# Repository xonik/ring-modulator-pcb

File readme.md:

# Yusynth Ring modulator

http://yusynth.net/Modular/EN/RINGMOD/index.html

All text is from Yusynth

## Description

The balanced modulator or four quadrant multiplier, is a great classical module. it provides the same functions as those of a ring modulator. Its main purpose is to generate  sounds with a complex overtone content such as bell sounds and other klang tones !
The principle of this circuit is based on a Gilbert cell (see references at the end of this page) contained in the classical LM1496 IC.

Basically, if one feeds the A input with a sinewave with frequency f1, that is sin(2πf1), and the B input with a sinewave with frequenc f2, that is sin(2πf2), one gets at the output the product these two signals, that is sin(2πf1) x sin(2πf2).

Due to trigonomic properties it reads :

 sin(2πf1) x sin(2πf2) = sin(2π(f1+f2)) + sin(2π(f1-f2))

in other words the output is a mixture of two sinewaves, one with frequency f1+f2 and the other with frequency f1-f2.

## Schematic

The schematic of this balanced modulator is directly inspired by that of the Elektor's Formant  (which is a mere adaptation of the application schematic of the LM1496 datasheet, see at the end of this page). I have only changed the values of the input resistors in order to make the input signal levels compatible with the Moog/Dotcom standards (10V peak to peak) I also added an output stage that amplifies the output signal by 6.8 in order to obtain 10Vpp.

## Settings and trimming

There are four trimmers to adjust : A1 to A4. These trimmers are used for cancelling the input signals. The settings are quite simple, you will need a signal generator that delivers a sinewave signal with a 10V (peak to peak) output amplitude. Here is how to proceed :
Tune the generator on 1000Hz and set the output level of the generator to 10Vpp.

Connect the output AxB (or CxD) of the module to an audio amplifier. Be sure to set the input potentiometer of the amplifier to a low value : the output level of the module is 10Vpp and most of the audio amplifiers expect an input level that doesn't exceed 1Vpp.
Connect the signal generator to the input A (or C) with a capacitor (AC-INPUT). There, you must hxear the 1000Hz signal at the output AxB (or CxD).

Adjust the trimmer A2 (or A4) such that the 1000Hz signal can no longer be heard at the output.

Disconnect the signal generator from input A (or C) and then connect the signal generator to the input B (or D)  with a capacitor (AC-INPUT). There, you must hear the 1000Hz signal at the output AxB (or CxD).
Adjust the trimmer A1 (or A3) such that the 1000Hz signal can no longer be heard at the output.

Now the module is ready to operate. A last check can be done by connecting the 1000Hz signal to both inputs A and B (AC inputs) : there you must hear a single signal of frequency twice as high (2000Hz).

**Comment (JT): A1 and A3 are the 470/500 ohm pots, A2 and A4 are 200/220 ohm.**

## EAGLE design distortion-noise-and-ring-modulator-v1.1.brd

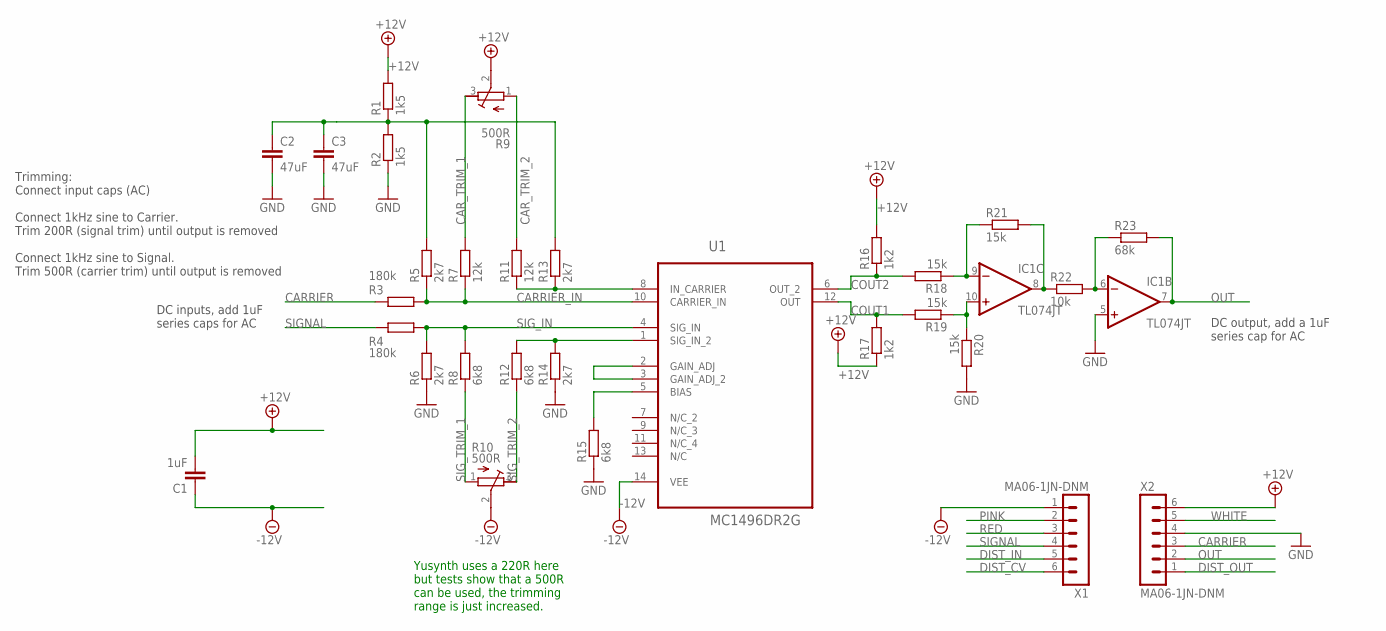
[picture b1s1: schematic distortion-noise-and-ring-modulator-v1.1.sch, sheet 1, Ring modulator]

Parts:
C1: 1uF; C0402-J
C2, C3: 47uF; C1206
IC1: TL074JT; TSSOP14J
R1, R2: 1k5; R0402
R3, R4: 180k; R0402
R5, R6, R13, R14: 2k7; R0603
R7, R11: 12k; R0402
R8, R12, R15: 6k8; R0603
R9, R10: 500R; RTRIM3296X
R16, R17: 1k2; R0603
R18, R19, R20, R21: 15k; R0402
R22: 10k; R0402
R23: 68k; R0603
U1: MC1496DR2G; SOIC127P600X175-14N
X1, X2: MA06-1JN-DNM; MA06N-1J

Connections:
+12V: C1.2, R1.2, R9.2 (S), R16.2, R17.1, X2.6; also elsewhere on the board
-12V: C1.1, R10.2 (S), U1.14 (VEE), X1.1; also elsewhere on the board
CARRIER: R3.1, X2.3
CARRIER_IN: R3.2, R5.1, R7.1, U1.10 (CARRIER_IN)
CAR_TRIM_1: R7.2, R9.3 (E)
CAR_TRIM_2: R9.1 (A), R11.2
COUT1: R17.2, R19.2, U1.12 (OUT)
COUT2: R16.1, R18.2, U1.6 (OUT_2)
DIST_CV: X1.6; also elsewhere on the board
DIST_IN: X1.5; also elsewhere on the board
DIST_OUT: X2.1; also elsewhere on the board
GND: C2.2, C3.2, IC1.5 (+IN), R2.1, R6.1, R14.1, R15.1, R20.2, X2.4; also elsewhere on the board
unnamed: R12.2, R14.2, U1.1 (SIG_IN_2)
unnamed: R11.1, R13.1, U1.8 (IN_CARRIER)
unnamed: C2.1, C3.1, R1.1, R2.2, R5.2, R13.2
unnamed: R15.2, U1.5 (BIAS)
unnamed: U1.2 (GAIN_ADJ), U1.3 (GAIN_ADJ_2)
unnamed: IC1.10 (+IN), R19.1, R20.1
unnamed: IC1.9 (-IN), R18.1, R21.1
unnamed: IC1.8 (OUT), R21.2, R22.1
unnamed: IC1.6 (-IN), R22.2, R23.1
OUT: IC1.7 (OUT), R23.2, X2.2
PINK: X1.2; also elsewhere on the board
RED: X1.3; also elsewhere on the board
SIGNAL: R4.1, X1.4
SIG_IN: R4.2, R6.2, R8.2, U1.4 (SIG_IN)
SIG_TRIM_1: R8.1, R10.1 (A)
SIG_TRIM_2: R10.3 (E), R12.1
WHITE: X2.5; also elsewhere on the board

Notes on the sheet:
DC inputs, add 1uF series caps for AC
DC output, add a 1uF series cap for AC
Trimming: Connect input caps (AC) Connect 1kHz sine to Carrier. Trim 200R (signal trim) until output is removed Connect 1kHz sine to Signal. Trim 500R (carrier trim) until output is removed
Yusynth uses a 220R here but tests show that a 500R can be used, the trimming range is just increased.

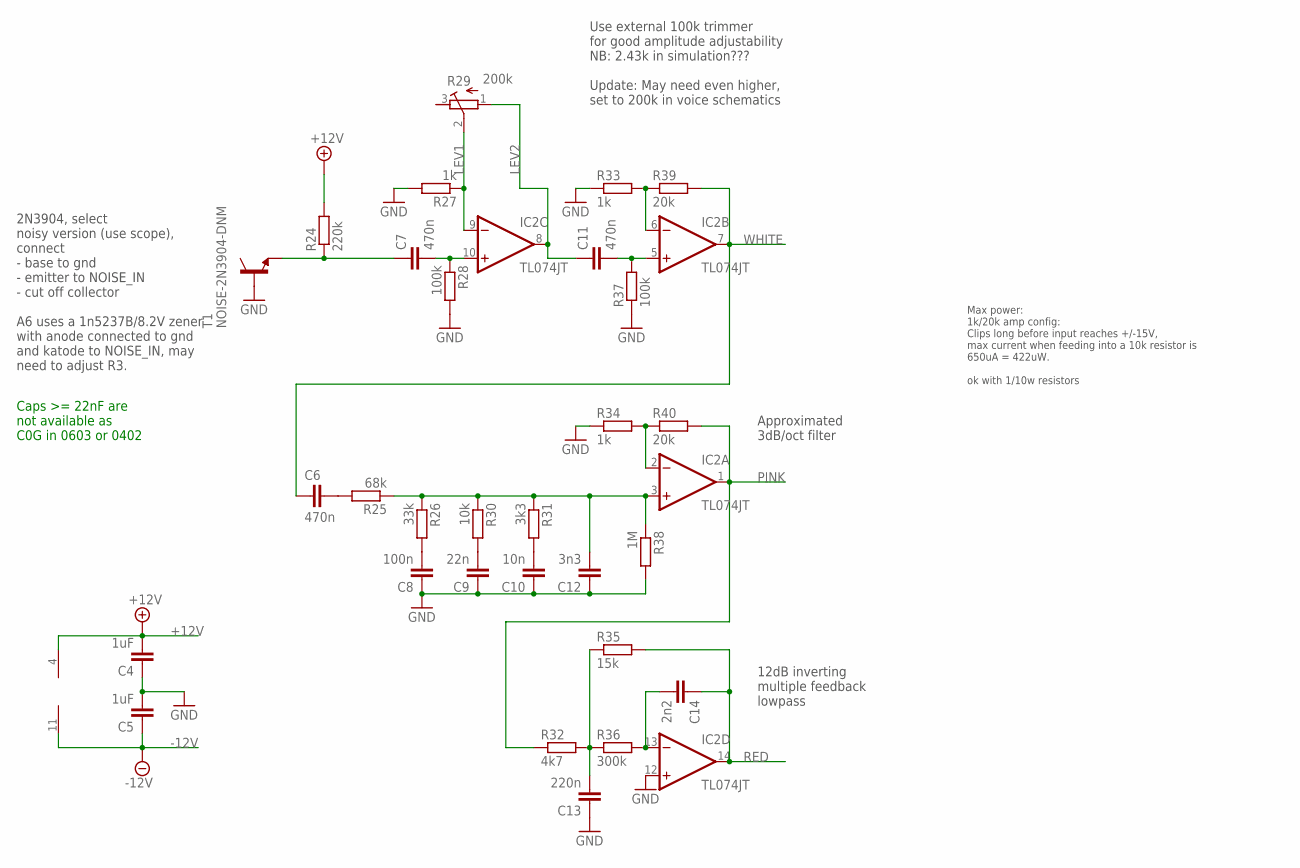
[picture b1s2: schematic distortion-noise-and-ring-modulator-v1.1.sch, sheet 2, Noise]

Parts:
C4, C5: 1uF; C0402-J
C6, C7, C11: 470n; C0603-J
C8: 100n; C0402-J
C9: 22n; C0402-J
C10: 10n; C0402-J
C12: 3n3; C0603-J
C13: 220n; C0402-J
C14: 2n2; C0603-J
IC2: TL074JT; TSSOP14J
R24: 220k; R0603
R25: 68k; R0603
R26: 33k; R0402
R27, R33, R34: 1k; R0402
R28, R37: 100k; R0402
R29: 200k; RTRIM3296W
R30: 10k; R0402
R31: 3k3; R0402
R32: 4k7; R0402
R35: 15k; R0402
R36: 300k; R0603
R38: 1M; R0402
R39, R40: 20k; R0402
T1: NOISE-2N3904-DNM; NOISE-2N3904-J

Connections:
+12V: C4.2, IC2.4 (V+), R24.2; also elsewhere on the board
-12V: C5.1, IC2.11 (V-); also elsewhere on the board
GND: C4.1, C5.2, C8.1, C9.1, C10.1, C12.1, C13.1, IC2.12 (+IN), R27.2, R28.2, R33.1, R34.1, R37.1, R38.2, T1.B; also elsewhere on the board
LEV1: IC2.9 (-IN), R27.1, R29.2 (S)
LEV2: C11.1, IC2.8 (OUT), R29.1 (A)
unnamed: IC2.2 (-IN), R34.2, R40.1
unnamed: IC2.6 (-IN), R33.2, R39.1
unnamed: C8.2, R26.2
unnamed: C9.2, R30.2
unnamed: C10.2, R31.2
unnamed: C7.1, R24.1, T1.E
unnamed: C7.2, IC2.10 (+IN), R28.1
unnamed: C11.2, IC2.5 (+IN), R37.2
unnamed: C12.2, IC2.3 (+IN), R25.1, R26.1, R30.1, R31.1, R38.1
unnamed: C6.2, R25.2
unnamed: C13.2, R32.2, R35.1, R36.1
unnamed: C14.2, IC2.13 (-IN), R36.2
PINK: IC2.1 (OUT), R32.1, R40.2; also elsewhere on the board
RED: C14.1, IC2.14 (OUT), R35.2; also elsewhere on the board
WHITE: C6.1, IC2.7 (OUT), R39.2; also elsewhere on the board

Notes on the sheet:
Use external 100k trimmer for good amplitude adjustability NB: 2.43k in simulation??? Update: May need even higher, set to 200k in voice schematics
Approximated 3dB/oct filter
12dB inverting multiple feedback lowpass
2N3904, select noisy version (use scope), connect - base to gnd - emitter to NOISE_IN - cut off collector A6 uses a 1n5237B/8.2V zener with anode connected to gnd and katode to NOISE_IN, may need to adjust R3.
Max power: 1k/20k amp config: Clips long before input reaches +/-15V, max current when feeding into a 10k resistor is 650uA = 422uW. ok with 1/10w resistors
Caps >= 22nF are not available as C0G in 0603 or 0402

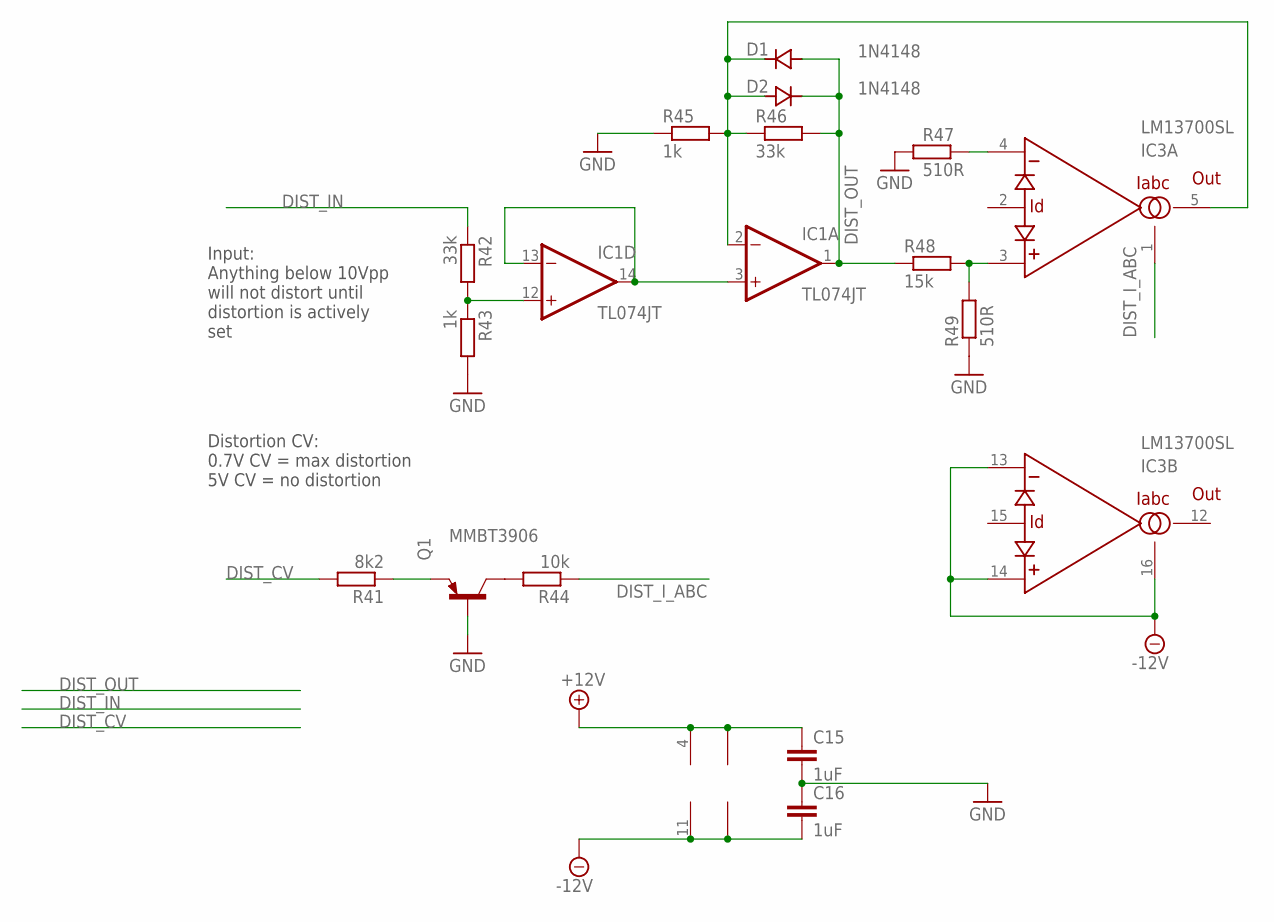
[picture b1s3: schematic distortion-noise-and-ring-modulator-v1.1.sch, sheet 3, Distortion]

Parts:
C15, C16: 1uF; C0402-J
D1, D2: 1N4148; SOD323J
IC1: TL074JT; TSSOP14J
IC3: LM13700SL; SO16-NARROW-J
Q1: MMBT3906; SOT23-BEC
R41: 8k2; R0603
R42, R46: 33k; R0402
R43, R45: 1k; R0402
R44: 10k; R0402
R47, R49: 510R; R0402
R48: 15k; R0402

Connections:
+12V: C15.1, IC1.4 (V+), IC3.11 (V+); also elsewhere on the board
-12V: C16.2, IC1.11 (V-), IC3.6 (V-), IC3.13 (-IN), IC3.14 (+IN), IC3.16 (IABC); also elsewhere on the board
DIST_CV: R41.2; also elsewhere on the board
DIST_IN: R42.1; also elsewhere on the board
DIST_I_ABC: IC3.1 (IABC), R44.1
DIST_OUT: D1.2 (A), D2.1 (C), IC1.1 (OUT), R46.2, R48.1; also elsewhere on the board
GND: C15.2, C16.1, Q1.B, R43.2, R45.1, R47.1, R49.1; also elsewhere on the board
unnamed: IC1.12 (+IN), R42.2, R43.1
unnamed: IC1.3 (+IN), IC1.13 (-IN), IC1.14 (OUT)
unnamed: D1.1 (C), D2.2 (A), IC1.2 (-IN), IC3.5 (OUT), R45.2, R46.1
unnamed: IC3.4 (-IN), R47.2
unnamed: IC3.3 (+IN), R48.2, R49.2
unnamed: Q1.E, R41.1
unnamed: Q1.C, R44.2

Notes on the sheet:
Distortion CV: 0.7V CV = max distortion 5V CV = no distortion
Input: Anything below 10Vpp will not distort until distortion is actively set

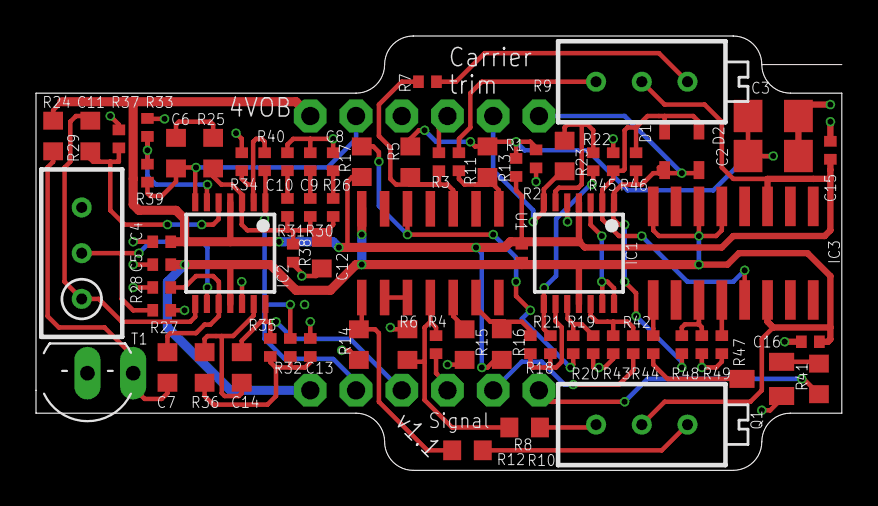
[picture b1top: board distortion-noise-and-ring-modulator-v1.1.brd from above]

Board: 2 copper layers, 44.8 x 24.1 mm, 75 parts (0 on the bottom side), 51 nets.

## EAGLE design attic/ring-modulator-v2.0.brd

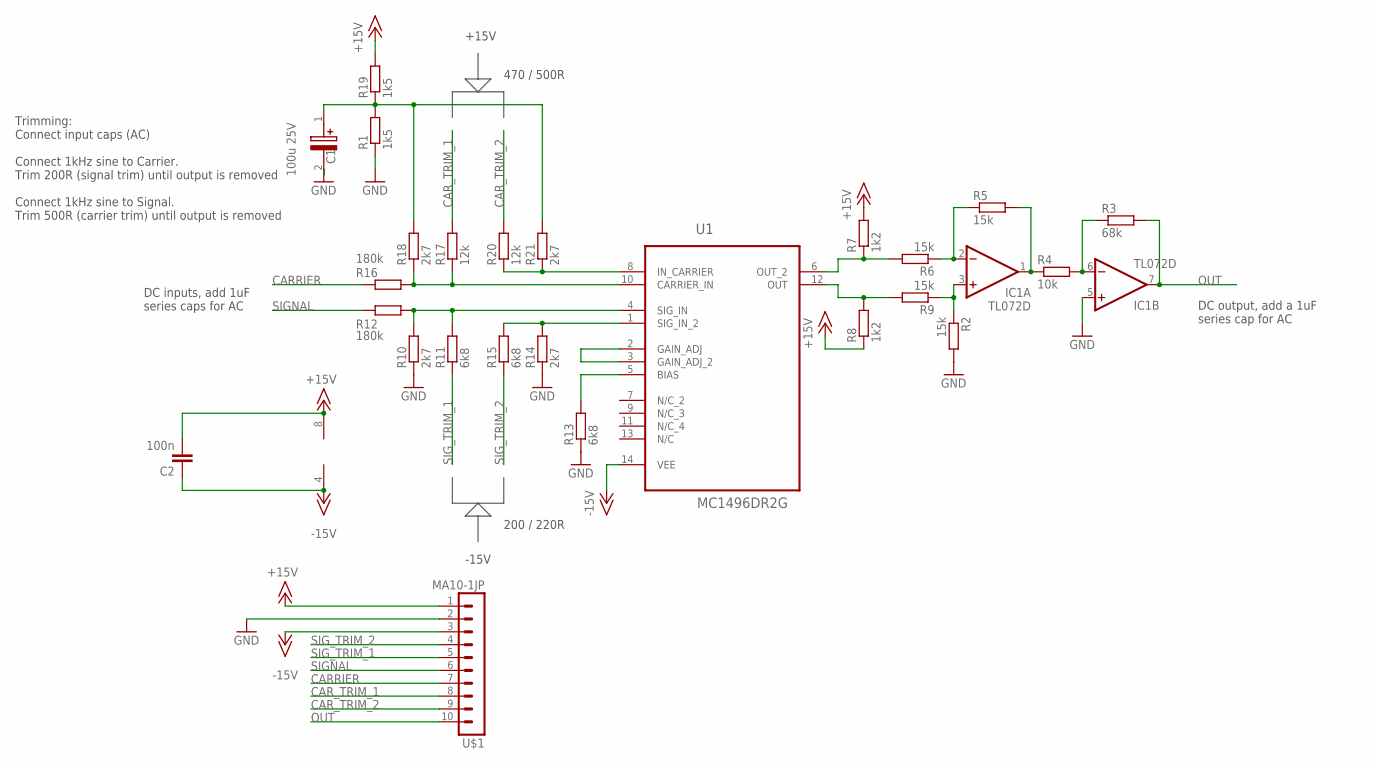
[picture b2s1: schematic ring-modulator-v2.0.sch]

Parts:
C1: 100u 25V; CAPAE660X610N
C2: 100n; C0603
IC1: TL072D; SO08J
R1, R19: 1k5; R0805
R2, R5, R6, R9: 15k; R0805
R3: 68k; R0805
R4: 10k; R0805
R7, R8: 1k2; R0805
R10, R14, R18, R21: 2k7; R0805
R11, R13, R15: 6k8; R0805
R12, R16: 180k; R0805
R17, R20: 12k; R0805
U1: MC1496DR2G; SOIC127P600X175-14N
U$1: MA10-1JP; SIP-PIN10-1J

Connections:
+15V: C2.2, IC1.8 (V+), R7.2, R8.1, R19.2, U$1.1
-15V: C2.1, IC1.4 (V-), U1.14 (VEE), U$1.3
CARRIER: R16.1, U$1.7
CAR_TRIM_1: R17.2, U$1.8
CAR_TRIM_2: R20.2, U$1.9
GND: C1.2 (-), IC1.5 (+IN), R1.1, R2.2, R10.1, R13.1, R14.1, U$1.2
unnamed: R10.2, R11.2, R12.2, U1.4 (SIG_IN)
unnamed: R16.2, R17.1, R18.1, U1.10 (CARRIER_IN)
unnamed: R14.2, R15.2, U1.1 (SIG_IN_2)
unnamed: R20.1, R21.1, U1.8 (IN_CARRIER)
unnamed: C1.1 (+), R1.2, R18.2, R19.1, R21.2
unnamed: R13.2, U1.5 (BIAS)
unnamed: U1.2 (GAIN_ADJ), U1.3 (GAIN_ADJ_2)
unnamed: R6.2, R7.1, U1.6 (OUT_2)
unnamed: R8.2, R9.2, U1.12 (OUT)
unnamed: IC1.3 (+IN), R2.1, R9.1
unnamed: IC1.2 (-IN), R5.1, R6.1
unnamed: IC1.1 (OUT), R4.1, R5.2
unnamed: IC1.6 (-IN), R3.1, R4.2
OUT: IC1.7 (OUT), R3.2, U$1.10
SIGNAL: R12.1, U$1.6
SIG_TRIM_1: R11.1, U$1.5
SIG_TRIM_2: R15.1, U$1.4

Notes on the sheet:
470 / 500R
+15V
200 / 220R
-15V
DC inputs, add 1uF series caps for AC
DC output, add a 1uF series cap for AC
Trimming: Connect input caps (AC) Connect 1kHz sine to Carrier. Trim 200R (signal trim) until output is removed Connect 1kHz sine to Signal. Trim 500R (carrier trim) until output is removed

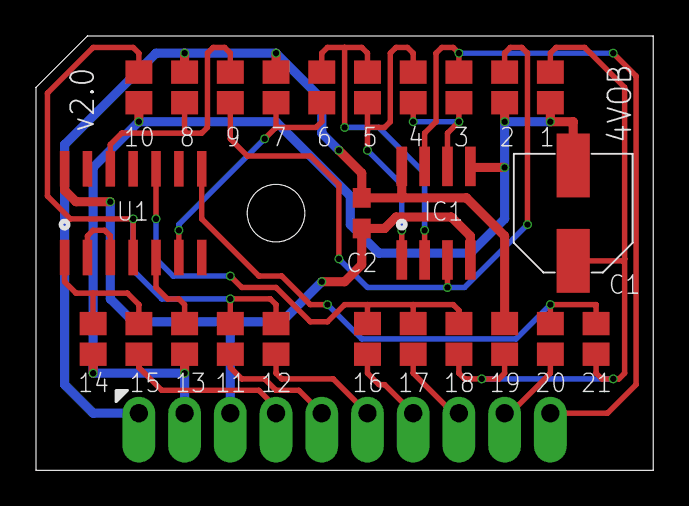
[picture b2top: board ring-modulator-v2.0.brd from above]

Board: 2 copper layers, 34.3 x 24.1 mm, 27 parts (1 on the bottom side), 23 nets.

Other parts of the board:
U$3: XONIK_LOGO_18

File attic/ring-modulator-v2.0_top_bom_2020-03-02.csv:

Comment,Designator,Footprint,LCSC Part #
1k2,R7 R8,R0805,C17379
1k5,R1 R19,R0805,C4310
2k7,R10 R14 R18 R21,R0805,C17530
6k8,R11 R13 R15,R0805,C17772
10k,R4,R0805,C17414
12k,R17 R20,R0805,C17444
15k,R2 R5 R6 R9,R0805,C17475
68k,R3,R0805,C17801
100n,C2,C0603,C14663
100u 25V,C1,CAPAE660X610N,C176675
180k,R12 R16,R0805,C17501
MC1496DR2G,U1,SOIC127P600X175-14N,C7295
TL072,IC1,SO08,C6961

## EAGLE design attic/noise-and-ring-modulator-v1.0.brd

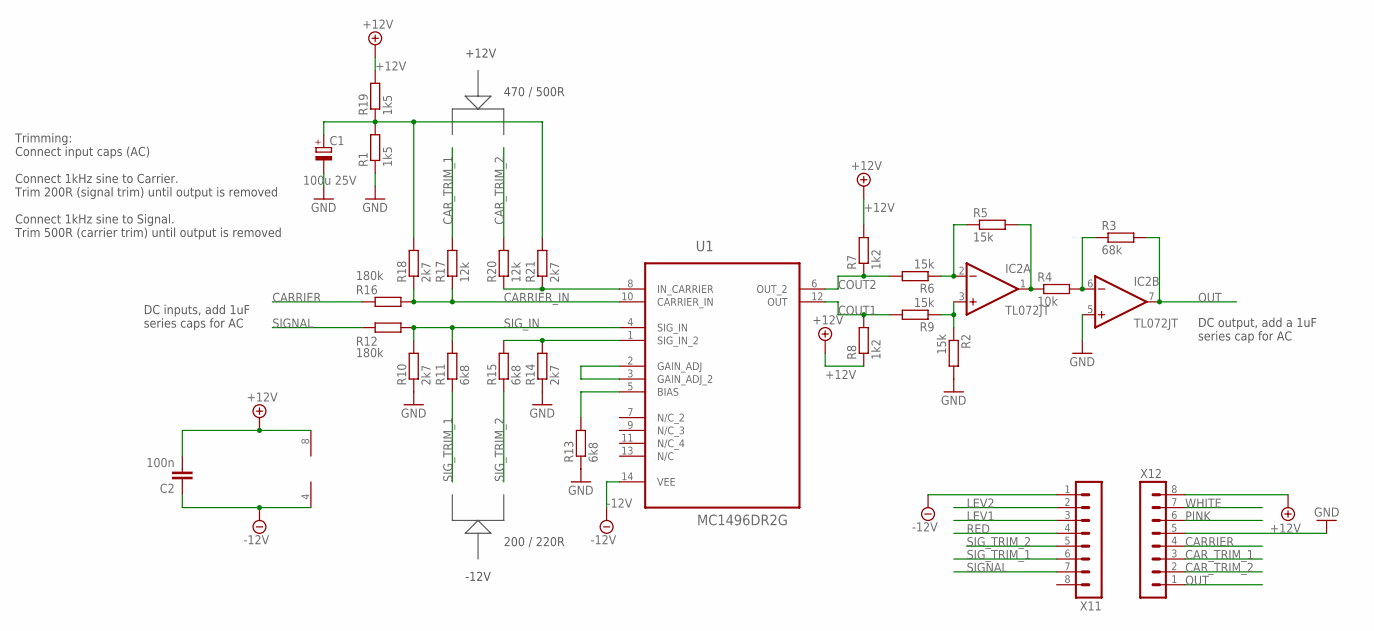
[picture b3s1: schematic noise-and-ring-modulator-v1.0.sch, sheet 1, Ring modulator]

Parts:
C1: 100u 25V; UD-4X5,8_NICHICON
C2: 100n; C0402-J
IC2: TL072JT; TSSOP8J
R1, R19: 1k5; R0402
R2, R5, R6, R9: 15k; R0402
R3: 68k; R0402
R4: 10k; R0402
R7, R8: 1k2; R0402
R10, R14, R18, R21: 2k7; R0402
R11, R13, R15: 6k8; R0402
R12, R16: 180k; R0402
R17, R20: 12k; R0402
U1: MC1496DR2G; SOIC127P600X175-14N
X11, X12: MA08-1JN; MA08N-1J

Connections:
+12V: C2.2, IC2.8 (V+), R7.2, R8.1, R19.2, X12.8; also elsewhere on the board
-12V: C2.1, IC2.4 (V-), U1.14 (VEE), X11.1; also elsewhere on the board
CARRIER: R16.1, X12.4
CARRIER_IN: R16.2, R17.1, R18.1, U1.10 (CARRIER_IN)
CAR_TRIM_1: R17.2, X12.3
CAR_TRIM_2: R20.2, X12.2
COUT1: R8.2, R9.2, U1.12 (OUT)
COUT2: R6.2, R7.1, U1.6 (OUT_2)
GND: C1.-, IC2.5 (+IN), R1.1, R2.2, R10.1, R13.1, R14.1, X12.5; also elsewhere on the board
LEV1: X11.3; also elsewhere on the board
LEV2: X11.2; also elsewhere on the board
unnamed: R14.2, R15.2, U1.1 (SIG_IN_2)
unnamed: R20.1, R21.1, U1.8 (IN_CARRIER)
unnamed: C1.+, R1.2, R18.2, R19.1, R21.2
unnamed: R13.2, U1.5 (BIAS)
unnamed: U1.2 (GAIN_ADJ), U1.3 (GAIN_ADJ_2)
unnamed: IC2.3 (+IN), R2.1, R9.1
unnamed: IC2.2 (-IN), R5.1, R6.1
unnamed: IC2.1 (OUT), R4.1, R5.2
unnamed: IC2.6 (-IN), R3.1, R4.2
OUT: IC2.7 (OUT), R3.2, X12.1
PINK: X12.6; also elsewhere on the board
RED: X11.4; also elsewhere on the board
SIGNAL: R12.1, X11.7
SIG_IN: R10.2, R11.2, R12.2, U1.4 (SIG_IN)
SIG_TRIM_1: R11.1, X11.6
SIG_TRIM_2: R15.1, X11.5
WHITE: X12.7; also elsewhere on the board

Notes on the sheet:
470 / 500R
+12V
200 / 220R
-12V
DC inputs, add 1uF series caps for AC
DC output, add a 1uF series cap for AC
Trimming: Connect input caps (AC) Connect 1kHz sine to Carrier. Trim 200R (signal trim) until output is removed Connect 1kHz sine to Signal. Trim 500R (carrier trim) until output is removed

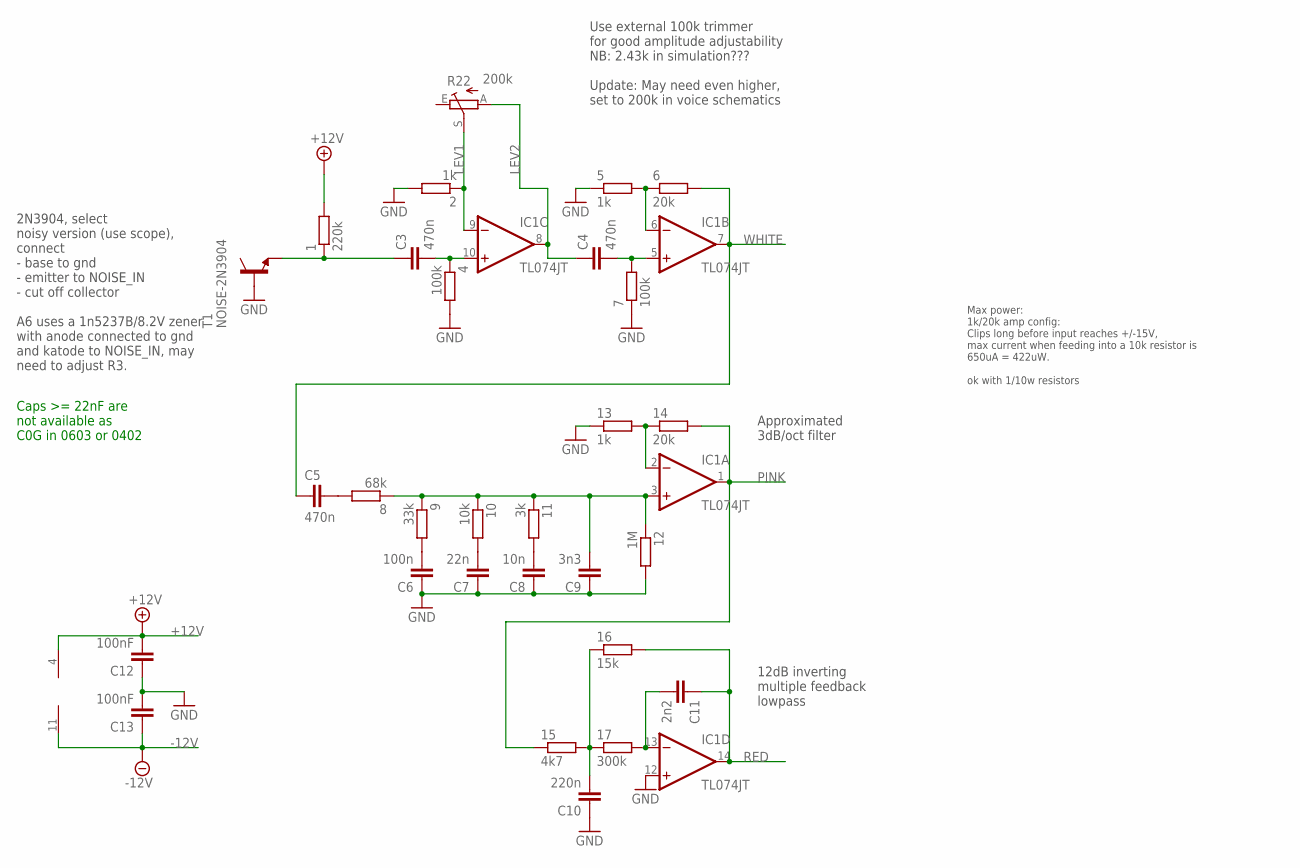
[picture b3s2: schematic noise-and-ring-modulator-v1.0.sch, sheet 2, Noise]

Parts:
1: 220k; R0402
2, 5, 13: 1k; R0402
4, 7: 100k; R0402
6, 14: 20k; R0402
8: 68k; R0402
9: 33k; R0402
10: 10k; R0402
11: 3k; R0402
12: 1M; R0402
15: 4k7; R0402
16: 15k; R0402
17: 300k; R0402
C3, C4, C5: 470n; C0402-J
C6: 100n; C0402-J
C7: 22n; C0402-J
C8: 10n; C0402-J
C9: 3n3; C0402-J
C10: 220n; C0402-J
C11: 2n2; C0402-J
C12, C13: 100nF; C0402-J
IC1: TL074JT; TSSOP14J
R22: 200k; S64W
T1: NOISE-2N3904; NOISE-2N3904-J

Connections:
+12V: 1.2, C12.2, IC1.4 (V+); also elsewhere on the board
-12V: C13.1, IC1.11 (V-); also elsewhere on the board
GND: 2.2, 4.2, 5.1, 7.1, 12.2, 13.1, C6.1, C7.1, C8.1, C9.1, C10.1, C12.1, C13.2, IC1.12 (+IN), T1.B; also elsewhere on the board
LEV1: 2.1, IC1.9 (-IN), R22.S; also elsewhere on the board
LEV2: C4.1, IC1.8 (OUT), R22.A; also elsewhere on the board
unnamed: 13.2, 14.1, IC1.2 (-IN)
unnamed: 5.2, 6.1, IC1.6 (-IN)
unnamed: 9.2, C6.2
unnamed: 10.2, C7.2
unnamed: 11.2, C8.2
unnamed: 1.1, C3.1, T1.E
unnamed: 4.1, C3.2, IC1.10 (+IN)
unnamed: 7.2, C4.2, IC1.5 (+IN)
unnamed: 8.1, 9.1, 10.1, 11.1, 12.1, C9.2, IC1.3 (+IN)
unnamed: 8.2, C5.2
unnamed: 15.2, 16.1, 17.1, C10.2
unnamed: 17.2, C11.2, IC1.13 (-IN)
PINK: 14.2, 15.1, IC1.1 (OUT); also elsewhere on the board
RED: 16.2, C11.1, IC1.14 (OUT); also elsewhere on the board
WHITE: 6.2, C5.1, IC1.7 (OUT); also elsewhere on the board

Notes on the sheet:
Use external 100k trimmer for good amplitude adjustability NB: 2.43k in simulation??? Update: May need even higher, set to 200k in voice schematics
Approximated 3dB/oct filter
12dB inverting multiple feedback lowpass
2N3904, select noisy version (use scope), connect - base to gnd - emitter to NOISE_IN - cut off collector A6 uses a 1n5237B/8.2V zener with anode connected to gnd and katode to NOISE_IN, may need to adjust R3.
Max power: 1k/20k amp config: Clips long before input reaches +/-15V, max current when feeding into a 10k resistor is 650uA = 422uW. ok with 1/10w resistors
Caps >= 22nF are not available as C0G in 0603 or 0402

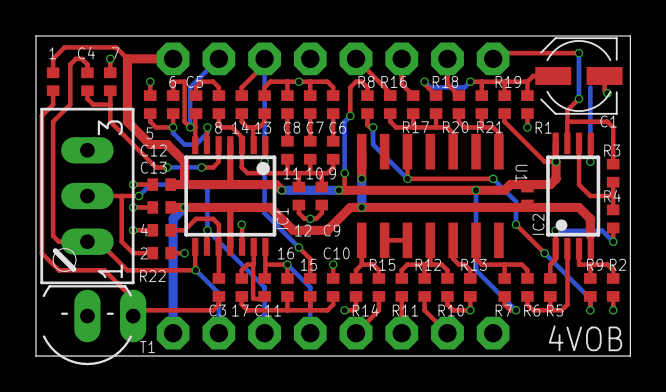
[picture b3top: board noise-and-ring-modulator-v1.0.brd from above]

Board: 2 copper layers, 33.0 x 17.8 mm, 57 parts (0 on the bottom side), 40 nets.

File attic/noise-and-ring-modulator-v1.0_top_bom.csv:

Comment,Designator,Footprint,LCSC Part #
MA08N-1J,X11 X12,MA08N-1J,
1M,12,R0402,
1k,2 5 13,R0402,
1k2,R7 R8,R0402,
1k5,R1 R19,R0402,
2k7,R10 R14 R18 R21,R0402,
2n2,C11,C0402-J,
3k,11,R0402,
3n3,C9,C0402-J,
4k7,15,R0402,
6k8,R11 R13 R15,R0402,
10k,10 R4,R0402,
10n,C8,C0402-J,
12k,R17 R20,R0402,
15k,16 R2 R5 R6 R9,R0402,
20k,6 14,R0402,
22n,C7,C0402-J,
33k,9,R0402,
68k,8 R3,R0402,
100k,4 7,R0402,
100n,C2 C6,C0402-J,
100nF,C12 C13,C0402-J,
100u 25V,C1,UD-4X5,8_NICHICON,
180k,R12 R16,R0402,
200k,R22,S64W,
220k,1,R0402,
220n,C10,C0402-J,
300k,17,R0402,
470n,C3 C4 C5,C0402-J,
MC1496DR2G,U1,SOIC127P600X175-14N,
NOISE-2N3904,T1,NOISE-2N3904-J,
TL072JT,IC2,TSSOP8J,
TL074JT,IC1,TSSOP14J,

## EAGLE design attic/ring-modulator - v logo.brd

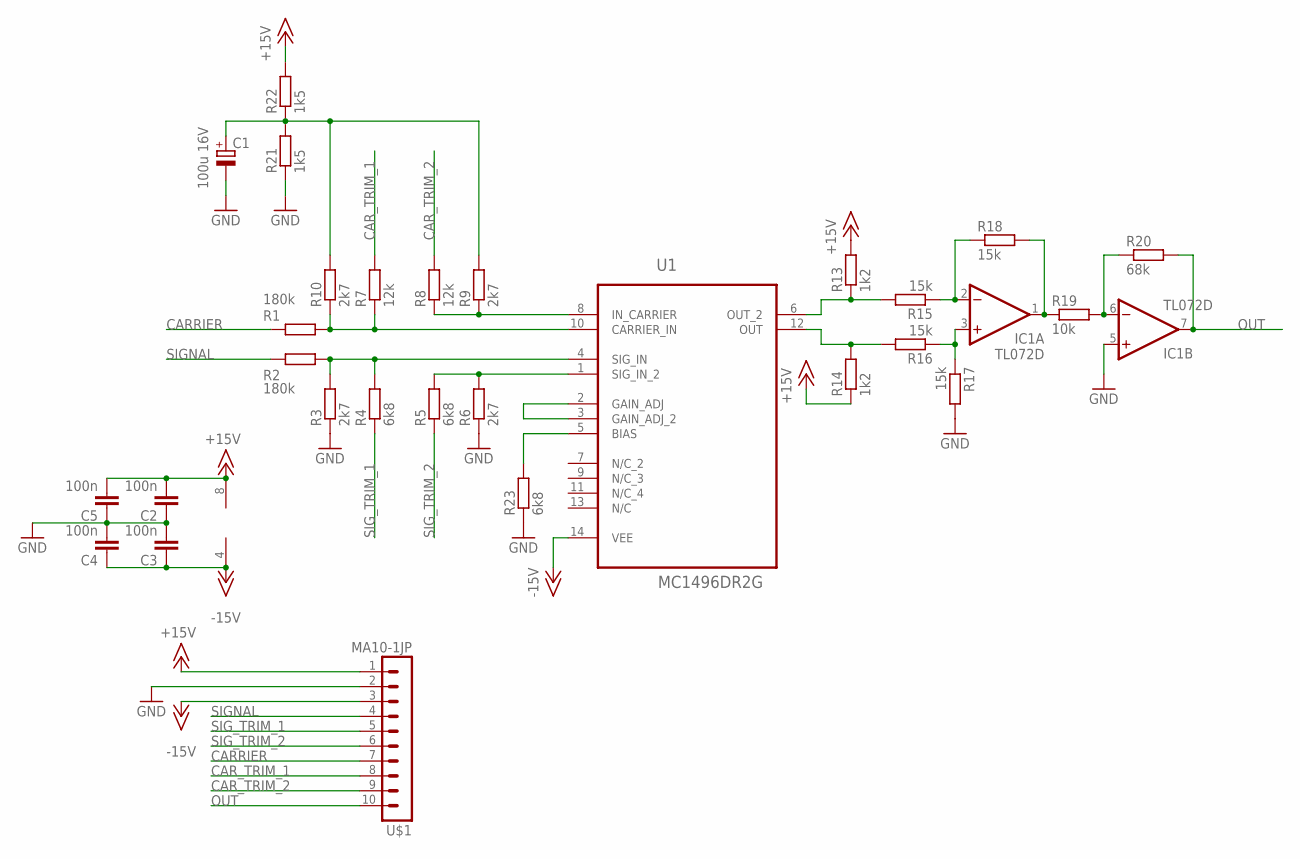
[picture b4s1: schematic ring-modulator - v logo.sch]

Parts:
C1: 100u 16V; E2,5-5
C2, C3, C4, C5: 100n; C0805
IC1: TL072D; SO08J
R1, R2: 180k; R0805
R3, R6, R9, R10: 2k7; R0805
R4, R5, R23: 6k8; R0805
R7, R8: 12k; R0805
R13, R14: 1k2; R0805
R15, R16, R17, R18: 15k; R0805
R19: 10k; R0805
R20: 68k; R0805
R21, R22: 1k5; R0805
U1: MC1496DR2G; SOIC127P600X175-14N
U$1: MA10-1JP; SIP-PIN10-1J

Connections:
+15V: C2.2, C5.2, IC1.8 (V+), R13.2, R14.1, R22.2, U$1.1
-15V: C3.1, C4.1, IC1.4 (V-), U1.14 (VEE), U$1.3
CARRIER: R1.1, U$1.7
CAR_TRIM_1: R7.2, U$1.8
CAR_TRIM_2: R8.2, U$1.9
GND: C1.-, C2.1, C3.2, C4.2, C5.1, IC1.5 (+IN), R3.1, R6.1, R17.2, R21.1, R23.1, U$1.2
unnamed: R2.2, R3.2, R4.2, U1.4 (SIG_IN)
unnamed: R1.2, R7.1, R10.1, U1.10 (CARRIER_IN)
unnamed: R5.2, R6.2, U1.1 (SIG_IN_2)
unnamed: R8.1, R9.1, U1.8 (IN_CARRIER)
unnamed: C1.+, R9.2, R10.2, R21.2, R22.1
unnamed: R23.2, U1.5 (BIAS)
unnamed: U1.2 (GAIN_ADJ), U1.3 (GAIN_ADJ_2)
unnamed: R13.1, R15.2, U1.6 (OUT_2)
unnamed: R14.2, R16.2, U1.12 (OUT)
unnamed: IC1.3 (+IN), R16.1, R17.1
unnamed: IC1.2 (-IN), R15.1, R18.1
unnamed: IC1.1 (OUT), R18.2, R19.1
unnamed: IC1.6 (-IN), R19.2, R20.1
OUT: IC1.7 (OUT), R20.2, U$1.10
SIGNAL: R2.1, U$1.4
SIG_TRIM_1: R4.1, U$1.5
SIG_TRIM_2: R5.1, U$1.6

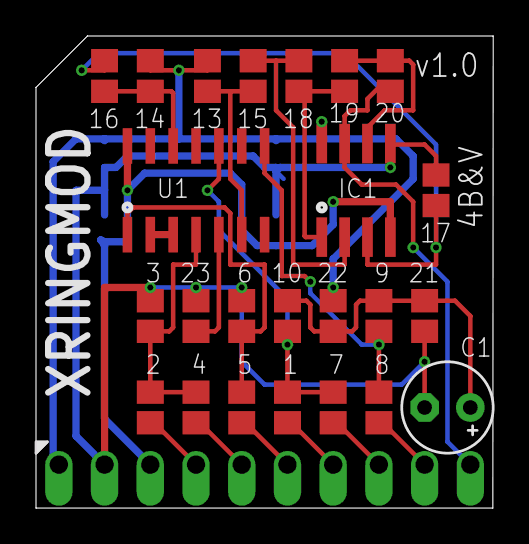
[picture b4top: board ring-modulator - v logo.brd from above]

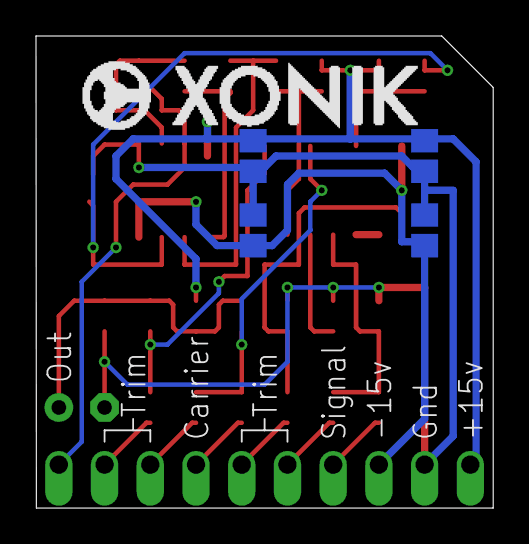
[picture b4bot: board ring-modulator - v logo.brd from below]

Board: 2 copper layers, 25.4 x 26.2 mm, 29 parts (4 on the bottom side), 23 nets.

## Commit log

2018-07-28 Fully traced ring modulator
2018-07-31 Part and connector names
2018-08-02 Added logo
2018-08-07 Redid board to v1.1, only two rows of resistors instead of 3. Feels much better.
2020-02-16 Version 2, new ground plane, corrected entry point for smd resistors++, added screw hole, added smd elec. cap
2020-02-16 Fixed silk screening, only missing xonik logo
2020-02-17 Added vector logo
2020-02-18 Added smd assembly bom etc
2020-02-20 Added info about external trimmers
2020-02-22 Changed to logo-as-component
2020-02-22 Slight silk adjustment
2020-02-23 Added documentation from yusynth.net
2020-03-02 Added updated BOM and gerber
2022-04-08 moving
2023-12-29 v3, trying to fit noise and ringmod on one chip
2023-12-29 V1.0 of combined noise and ringmod module
2023-12-29 Fixed silk screen noise/ringmod
2023-12-29 Tiny silk screen fix
2023-12-29 Replaced pin footprints
2023-12-29 removed some silk screen
2023-12-30 Combined noise, rm and distortion
2023-12-30 Added bom and checked parts and pcb with JLCPCB
2024-04-14 v1.1 of combined FX module with trimmers onboard
2024-04-14 Removed all external trimmers
2024-04-14 A bit more gnd
2024-04-14 Nude pin headers
2024-04-19 Replaced 100uf electrolytic cap with two ceramic. Changed 200R to 500R pot to get a single extended part
2024-04-19 Comments
2024-05-18 Changed to 3k3 on pink filter output to save cost with JLCPCB
2024-05-26 cleanup
2024-05-31 Image update
2024-06-02 Tested with JLCPCB
2024-06-03 Fixed 1uF caps
2024-06-04 Removed unused connections
2024-06-06 Replaced several parts with 0603 to be able to use basic parts
2024-06-06 More basic parts
2024-06-21 Rounded corners
2024-06-23 V1.1 ready for production
2024-06-25 Increased via outer diameter
2025-01-01 Moved multi fx to separate repo
